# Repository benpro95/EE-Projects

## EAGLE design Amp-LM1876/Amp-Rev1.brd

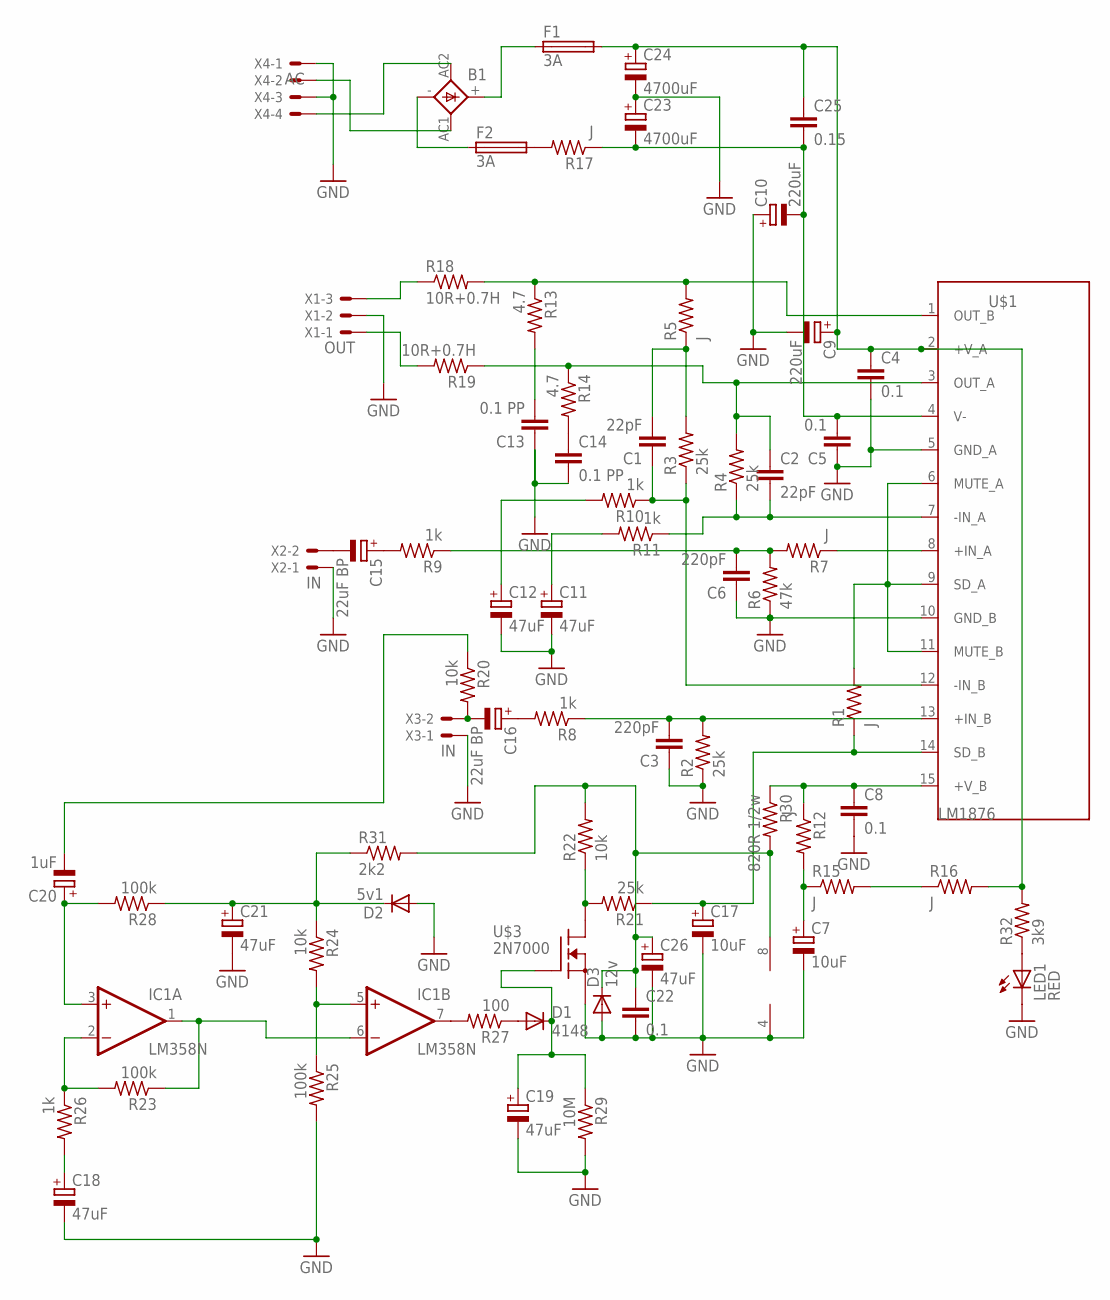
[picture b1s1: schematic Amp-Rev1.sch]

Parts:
B1: GBU4; GBU4S
C1, C2: 22pF; C075-032X103
C3, C6: 220pF; C1210
C4, C5, C8: 0.1; C050-025X075
C7: 10uF; E2,5-7
C9, C10: 220uF; E5-8,5
C11, C12, C18, C19, C21, C26: 47uF; E2,5-7
C13, C14: 0.1 PP; C050-055X075
C15, C16: 22uF BP; E2,5-7
C17: 10uF; E2,5-6
C20: 1uF; E2,5-6
C22: 0.1; C1206
C23, C24: 4700uF; E7,5-16
C25: 0.15; C075-032X103
D1: 4148; DO35-7
D2: 5v1; DO35-10
D3: 12v; DO35-10
F1, F2: 3A; 19560
IC1: LM358N; DIL08
LED1: RED; LED3MM
R1, R12, R15, R16: J; 0207/12
R2: 25k; R1210
R3, R4: 25k; 0207/10
R5, R17: J; 0207/10
R6: 47k; M1206
R7: J; 0204/7
R8, R11, R26: 1k; 0207/10
R9: 1k; 0207/12
R10: 1k; 0204/7
R13, R14: 4.7; 0207/12
R18, R19: 10R+0.7H; 0207/12
R20, R22: 10k; 0204/7
R21: 25k; 0204/7
R23, R25, R28: 100k; 0204/5
R24: 10k; 0207/10
R27: 100; 0204/7
R29: 10M; 0207/10
R30: 820R 1/2w; 0207/10
R31: 2k2; 0309/10
R32: 3k9; 0207/10
U$1: LM1876; MULTIWATT-15
U$3: 2N7000; TO92-
X1: OUT; 22-23-2031
X2, X3: IN; 22-23-2021
X4: AC; 5566-4

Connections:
GND: C3.1, C4.2, C5.1, C6.1, C7.-, C8.2, C9.-, C10.+, C11.-, C12.-, C13.1, C14.2, C17.-, C18.-, C19.-, C21.-, C22.2, C23.+, C24.-, C26.-, D2.A, D3.A, IC1.4 (V-), LED1.K (C), R2.1, R6.1, R25.2, R29.2, U$1.5 (GND_A), U$1.10 (GND_B), U$3.3 (S), X1.2, X2.1, X3.1, X4.1, X4.3
unnamed: R7.1, U$1.8 (+IN_A)
unnamed: R1.2, U$1.6 (MUTE_A), U$1.9 (SD_A), U$1.11 (MUTE_B)
unnamed: C1.2, R3.2, R5.1
unnamed: C6.2, R6.2, R7.2, R9.1
unnamed: C2.2, R4.1, R11.1, U$1.7 (-IN_A)
unnamed: C5.2, C10.-, C23.-, C25.2, R17.1, U$1.4 (V-)
unnamed: C2.1, R4.2, R14.1, R19.1, U$1.3 (OUT_A)
unnamed: C4.1, C9.+, C24.+, C25.1, F1.2, R16.2, R32.2, U$1.2 (+V_A)
unnamed: R5.2, R13.1, R18.2, U$1.1 (OUT_B)
unnamed: C1.1, R3.1, R10.1, U$1.12 (-IN_B)
unnamed: R15.2, R16.1
unnamed: C22.1, C26.+, D3.C, IC1.8 (V+), R22.2, R30.2, R31.2
unnamed: C7.+, R12.2, R15.1
unnamed: C17.+, R1.1, R21.1, U$1.14 (SD_B)
unnamed: C12.+, R10.2
unnamed: C11.+, R11.2
unnamed: C3.2, R2.2, R8.1, U$1.13 (+IN_B)
unnamed: C13.2, R13.2
unnamed: C14.1, R14.2
unnamed: R18.1, X1.3
unnamed: R19.2, X1.1
unnamed: C15.+, R9.2
unnamed: C15.-, X2.2
unnamed: C20.-, R20.1
unnamed: C16.+, R8.2
unnamed: C16.-, R20.2, X3.2
unnamed: LED1.A, R32.1
unnamed: C19.+, D1.C, R29.1, U$3.2 (G)
unnamed: IC1.2 (-IN), R23.2, R26.1
unnamed: IC1.1 (OUT), IC1.6 (-IN), R23.1
unnamed: C20.+, IC1.3 (+IN), R28.2
unnamed: IC1.5 (+IN), R24.2, R25.1
unnamed: C18.+, R26.2
unnamed: C8.1, R12.1, R30.1, U$1.15 (+V_B)
unnamed: IC1.7 (OUT), R27.2
unnamed: C21.+, D2.C, R24.1, R28.1, R31.1
unnamed: R21.2, R22.1, U$3.1 (D)
unnamed: D1.A, R27.1
unnamed: B1.+, F1.1
unnamed: F2.2, R17.2
unnamed: B1.-, F2.1
unnamed: B1.AC1 (AC2), X4.2
unnamed: B1.AC2 (AC1), X4.4

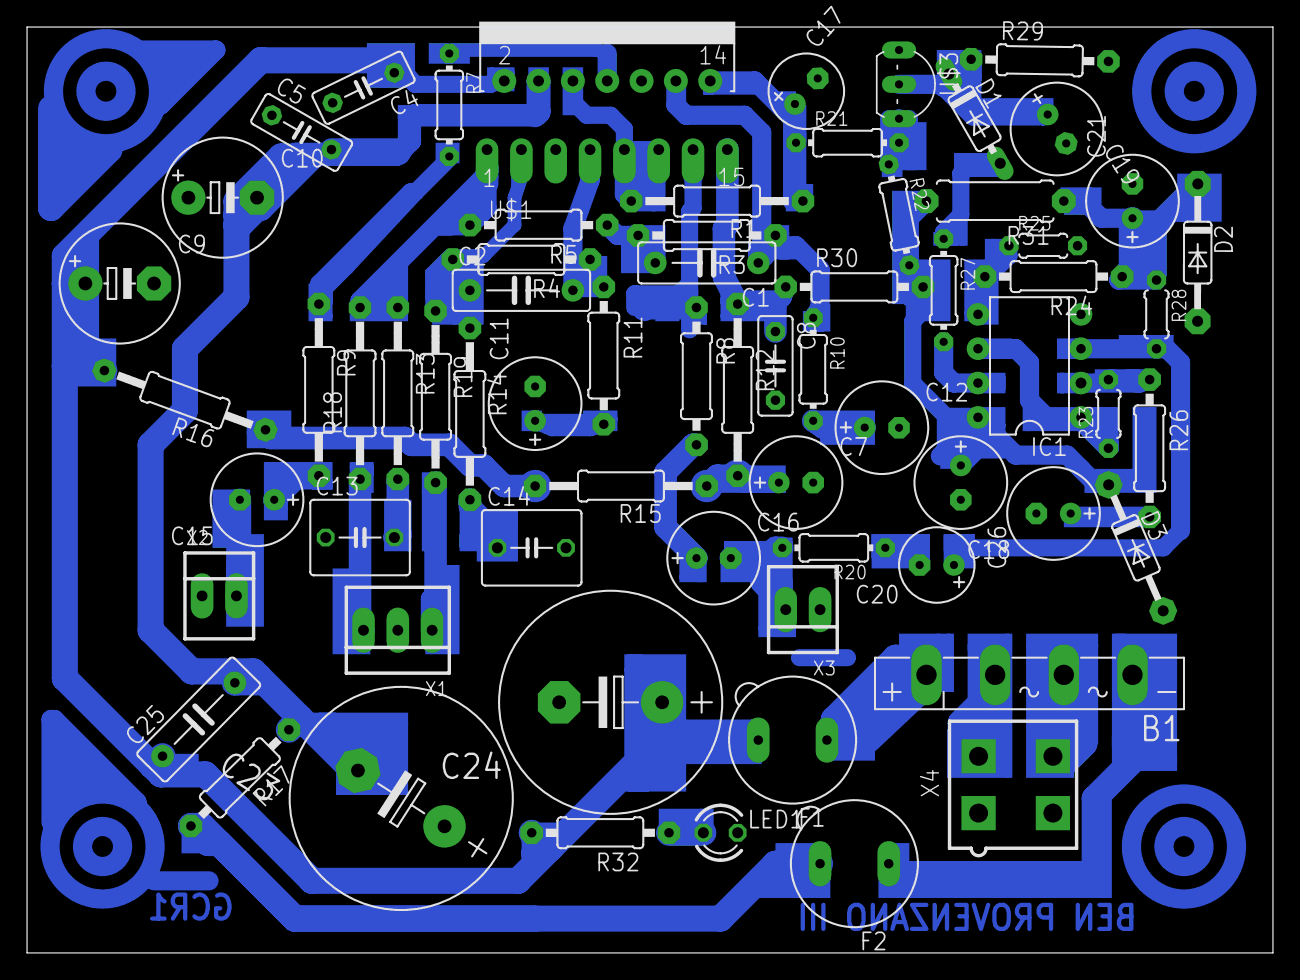
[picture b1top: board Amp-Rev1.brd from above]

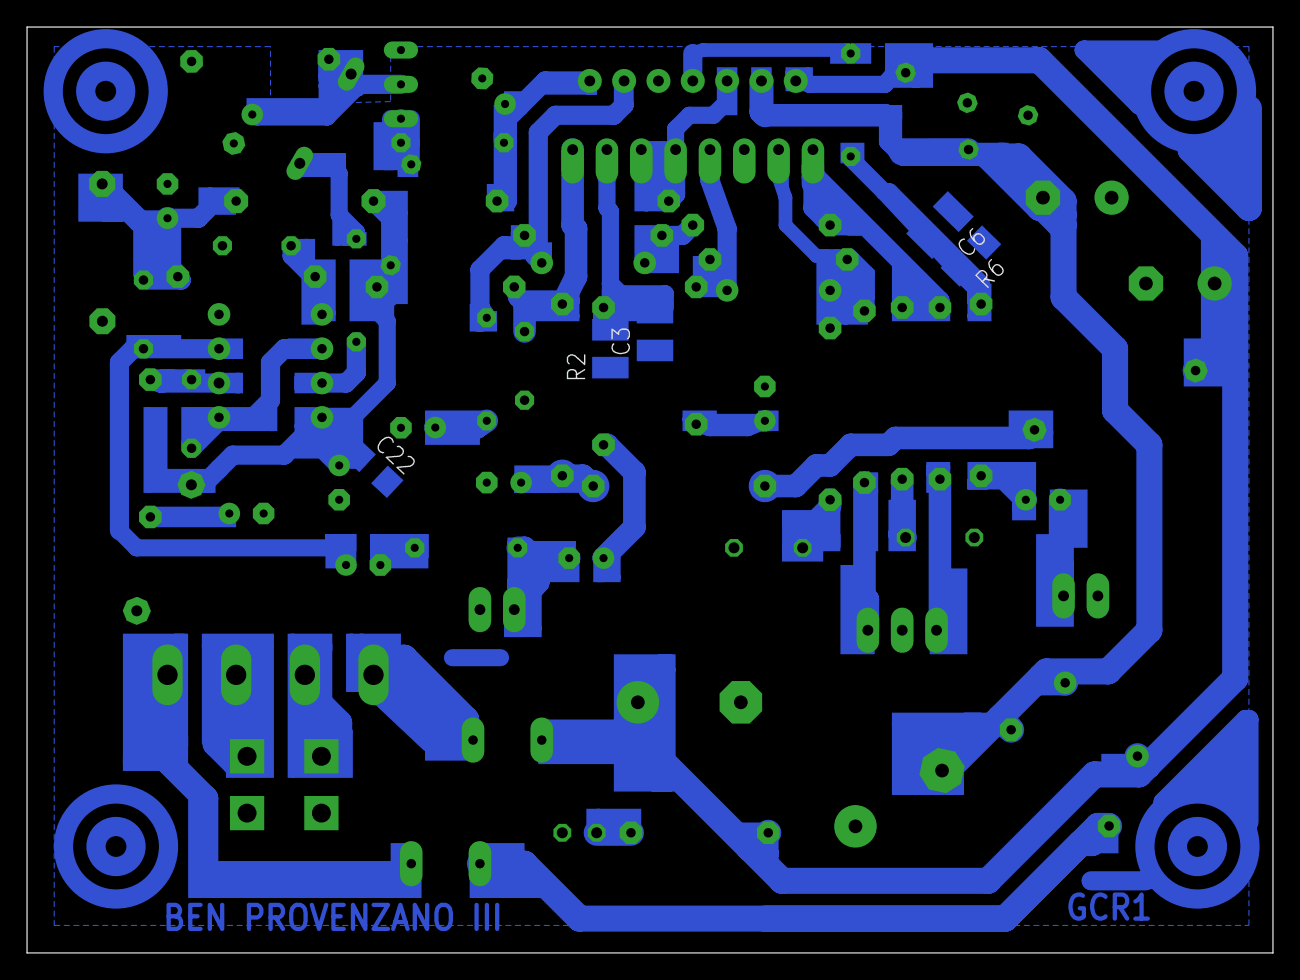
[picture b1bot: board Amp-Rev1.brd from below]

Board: 2 copper layers, 92.2 x 68.5 mm, 72 parts (5 on the bottom side), 44 nets.

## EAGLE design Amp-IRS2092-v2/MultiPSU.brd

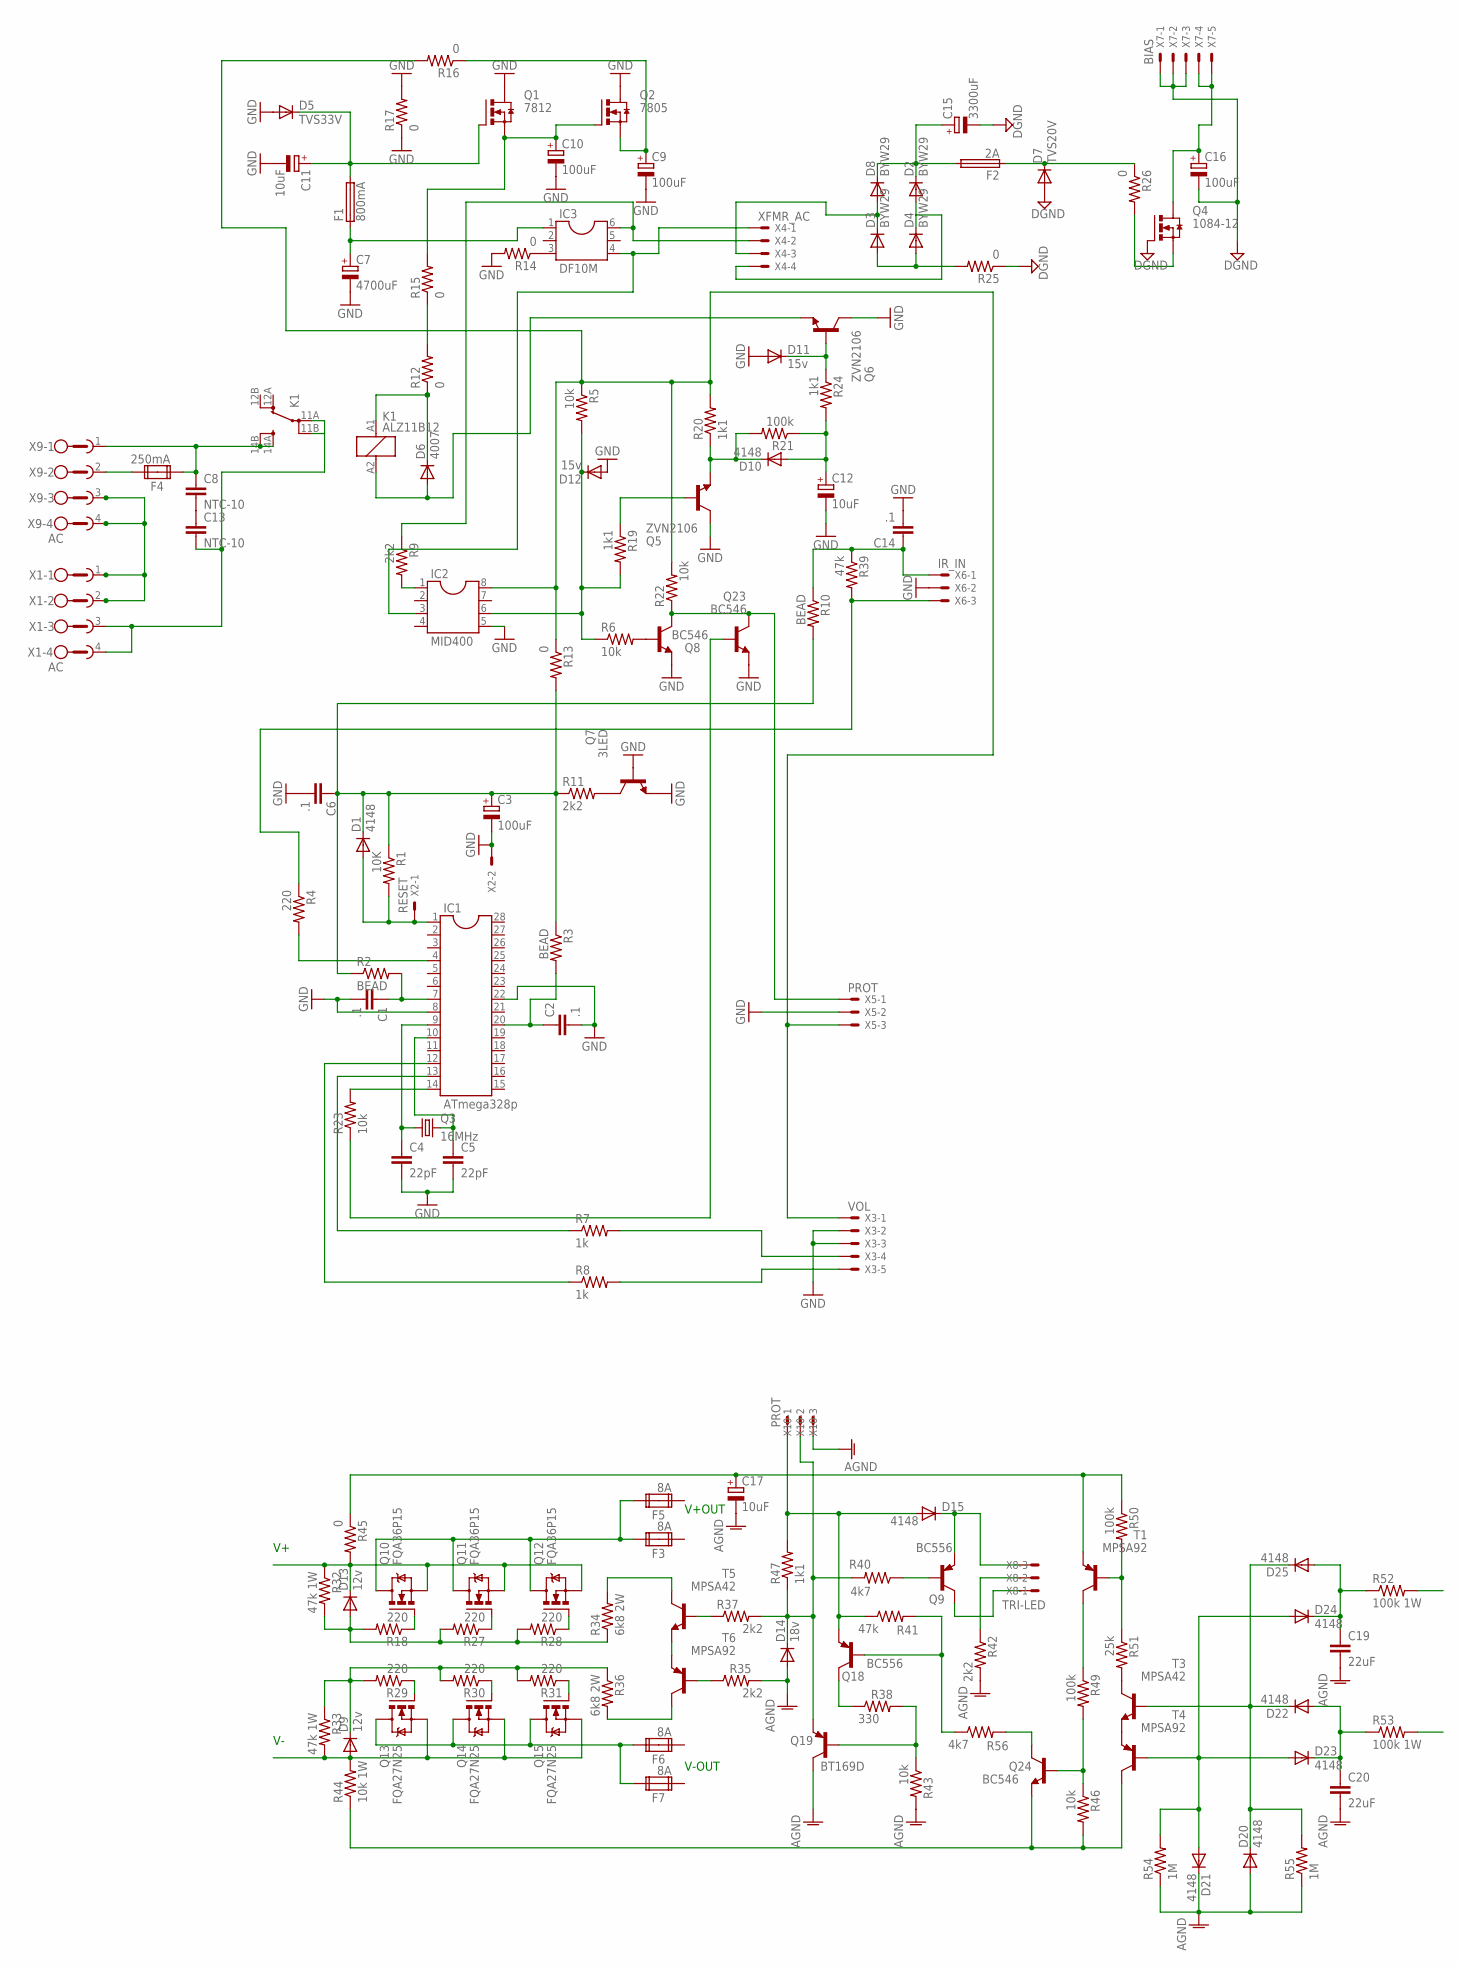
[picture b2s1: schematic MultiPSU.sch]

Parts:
C1, C2, C6, C14: .1; C1210K
C3, C9, C10, C16: 100uF; E3,5-10
C4, C5: 22pF; C1210K
C7: 4700uF; E7,5-16
C8, C13: NTC-10; C102-054X133
C11, C12, C17: 10uF; E3,5-10
C15: 3300uF; E7,5-16
C19, C20: 22uF; C050-075X075
D1, D20, D21, D22, D23, D24, D25: 4148; DO35-7
D2, D3, D4, D8: BYW29; DO220S
D5: TVS33V; SOD57-10
D6: 4007; DO41-10
D7: TVS20V; SOD57-10
D9, D13: 12v; DO41-10
D10: 4148; DO35-10
D11, D12: 15v; DO35-7
D14: 18v; DO41-10
D15: 4148; DO41-10
F1: 800mA; 19560
F2: 2A; 19560
F3, F5, F6, F7: 8A; FUSE1
F4: 250mA; FUSE1
IC1: ATmega328p; DIL28-3
IC2: MID400; DIL08
IC3: DF10M; DIL06
K1: ALZ11B12; RT-C/O16A5
Q1: 7812; TO220BH
Q2: 7805; TO220BH
Q3: 16MHz; HC49/S
Q4: 1084-12; TO220BH
Q5, Q6: ZVN2106; TO92-EBC
Q7: 3LED; TO92-EBC
Q8, Q23, Q24: BC546; TO92-EBC
Q9, Q18: BC556; TO92-EBC
Q10, Q11, Q12: FQA36P15; TO-247AD-H
Q13, Q14, Q15: FQA27N25; TO-247AD-H
Q19: BT169D; TO92-EBC
R1: 10K; 0309/10
R2, R10: BEAD; 0309/10
R3: BEAD; 0309/12
R4, R18, R27, R28, R29, R30, R31: 220; 0309/12
R5, R22, R43: 10k; 0309/10
R6: 10k; 0309/12
R7, R8: 1k; R1210
R9: 2k2; 0309/12
R11, R35, R37, R42: 2k2; 0309/10
R12, R14: 0; 0309/10
R13, R15, R16, R17, R25, R26, R45: 0; 0309/12
R19: 1k1; 0309/12
R20, R24, R47: 1k1; 0309/10
R21, R50: 100k; 0309/10
R23: 10k; R1210
R32, R33: 47k 1W; 0411/15
R34, R36: 6k8 2W; 0411/15
R38: 330; 0309/10
R39, R41: 47k; 0309/10
R40, R56: 4k7; 0309/10
R44: 10k 1W; 0411/15
R46: 10k; 0411/15
R49: 100k; 0411/15
R51: 25k; 0309/10
R52, R53: 100k 1W; 0309/10
R54, R55: 1M; R1210
T1, T4, T6: MPSA92; TO92-EBC
T3, T5: MPSA42; TO92-EBC
X1, X9: AC; GMSTBA4
X2: RESET; 22-23-2021
X3: VOL; 22-23-2051
X4: XFMR_AC; 5566-4
X5, X10: PROT; 22-23-2031
X6: IR_IN; 22-23-2031
X7: BIAS; 22-23-2051
X8: TRI-LED; 22-23-2031

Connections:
AGND: C17.-, C19.2, C20.2, D14.A, D20.A, D21.C, Q19.C, R35.2, R42.2, R43.2, R54.1, R55.1, X10.3
DGND: C15.-, C16.-, D7.A, Q4.G, R25.1, X7.1, X7.2, X7.3
GND: C1.2, C2.2, C3.-, C4.2, C5.2, C6.2, C7.-, C9.-, C10.-, C11.-, C12.-, C14.2, D5.A, D11.A, D12.A, IC1.8, IC1.22, IC2.5, Q1.D, Q2.D, Q5.C, Q6.C, Q7.B, Q7.E, Q8.E, Q23.E, R14.2, R17.1, R17.2, X2.2, X3.2, X3.3, X5.2, X6.2
unnamed: Q8.B, R6.2
unnamed: D1.A, IC1.1, R1.2, X2.1
unnamed: IC1.4, R4.2
unnamed: C2.1, IC1.20, R3.2
unnamed: R4.1, R39.2, X6.3
unnamed: IC1.13, R7.1
unnamed: IC1.12, R8.1
unnamed: C11.+, D5.C, F1.2, Q1.G
unnamed: C8.2, C13.1
unnamed: D6.C, K1.A1 (1), R12.1
unnamed: IC3.6, R9.1, X4.2
unnamed: C4.1, IC1.9, Q3.1
unnamed: C5.1, IC1.10, Q3.2
unnamed: X1.1, X1.2, X9.3, X9.4
unnamed: D12.C, IC2.6, R5.2, R6.1, R19.2
unnamed: IC2.1, R9.2
unnamed: Q8.C, Q23.C, R22.1, X5.1
unnamed: IC3.3, R14.1
unnamed: C14.1, R10.1, R39.1, X6.1
unnamed: F4.2A, X9.2
unnamed: Q7.C, R11.2
unnamed: C8.1, F4.1A, K1.14A (SA), K1.14B (SB), X9.1
unnamed: C13.2, K1.11A (PA), K1.11B (PB), X1.3, X1.4
unnamed: C9.+, Q2.S, R16.1
unnamed: C10.+, Q1.S, Q2.G, R15.2
unnamed: R12.2, R15.1
unnamed: C7.+, F1.1, IC3.1
unnamed: C3.+, C6.1, D1.C, R1.1, R2.1, R3.1, R10.2, R11.1, R13.2
unnamed: D3.C, D8.A, X4.3
unnamed: D2.A, D4.C, X4.4
unnamed: C1.1, IC1.7, R2.2
unnamed: IC2.8, R5.1, R13.1, R16.2, R20.2, R22.2, X3.1, X5.3
unnamed: IC2.3, IC3.4, X4.1
unnamed: Q5.B, R19.1
unnamed: D10.C, Q5.E, R20.1, R21.2
unnamed: C12.+, D10.A, R21.1, R24.2
unnamed: IC1.14, R23.2
unnamed: D6.A, K1.A2 (2), Q6.E
unnamed: D11.C, Q6.B, R24.1
unnamed: Q23.B, R23.1
unnamed: R8.2, X3.5
unnamed: R7.2, X3.4
unnamed: D3.A, D4.A, R25.2
unnamed: C15.+, D2.C, D8.C, F2.2
unnamed: D7.C, F2.1, R26.1
unnamed: Q4.S, R26.2
unnamed: D13.C, Q10.S, Q11.S, Q12.S, R32.1, R45.2
unnamed: F3.2A, F5.2A, Q10.D, Q11.D, Q12.D
unnamed: D9.A, Q13.S, Q14.S, Q15.S, R33.2, R44.2
unnamed: C16.+, Q4.D, X7.4, X7.5
unnamed: F6.2A, F7.2A, Q13.D, Q14.D, Q15.D
unnamed: Q10.G, R18.1
unnamed: Q11.G, R27.1
unnamed: Q12.G, R28.1
unnamed: Q13.G, R29.1
unnamed: Q14.G, R30.1
unnamed: Q15.G, R31.1
unnamed: D9.C, R29.2, R30.2, R31.2, R33.1, R36.1
unnamed: D13.A, R18.2, R27.2, R28.2, R32.2, R34.1
unnamed: R34.2, T5.C
unnamed: R36.2, T6.C
unnamed: T5.E, T6.E
unnamed: R35.1, T6.B
unnamed: R37.1, T5.B
unnamed: Q18.C, R38.1
unnamed: D14.C, Q19.E, R37.2, R40.2, R47.1, X10.2
unnamed: Q9.B, R40.1
unnamed: R42.1, X8.2
unnamed: Q19.B, R38.2, R43.1
unnamed: Q9.C, X8.1
unnamed: D15.C, Q9.E, X8.3
unnamed: Q24.E, R44.1, R46.2, T4.C
unnamed: R49.1, T1.C
unnamed: Q24.B, R46.1, R49.2
unnamed: C17.+, R45.1, R50.1, T1.E
unnamed: Q18.B, R41.2, R56.1
unnamed: R50.2, R51.1, T1.B
unnamed: R51.2, T3.C
unnamed: T3.E, T4.E
unnamed: D21.A, D23.A, D24.A, R54.2, T4.B
unnamed: D20.C, D22.C, D25.C, R55.2, T3.B
unnamed: C20.1, D22.A, D23.C, R53.1
unnamed: C19.1, D24.C, D25.A, R52.1
unnamed: Q24.C, R56.2
unnamed: D15.A, Q18.E, R41.1, R47.2, X10.1

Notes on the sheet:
V+OUT
V-OUT

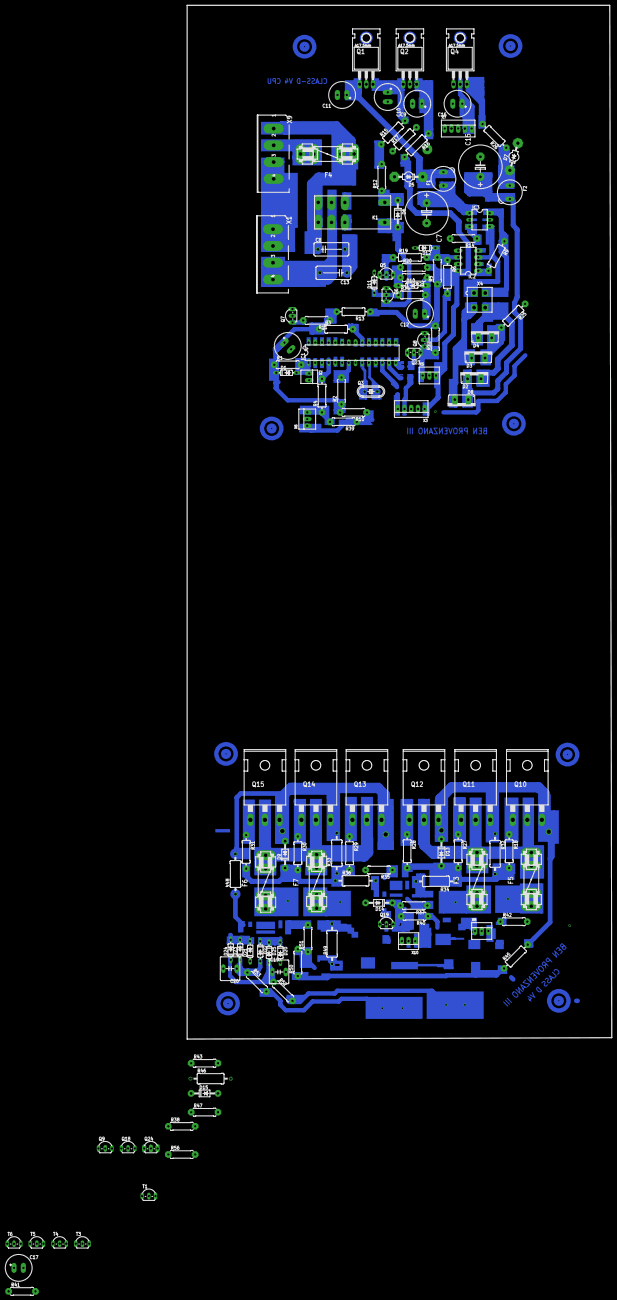
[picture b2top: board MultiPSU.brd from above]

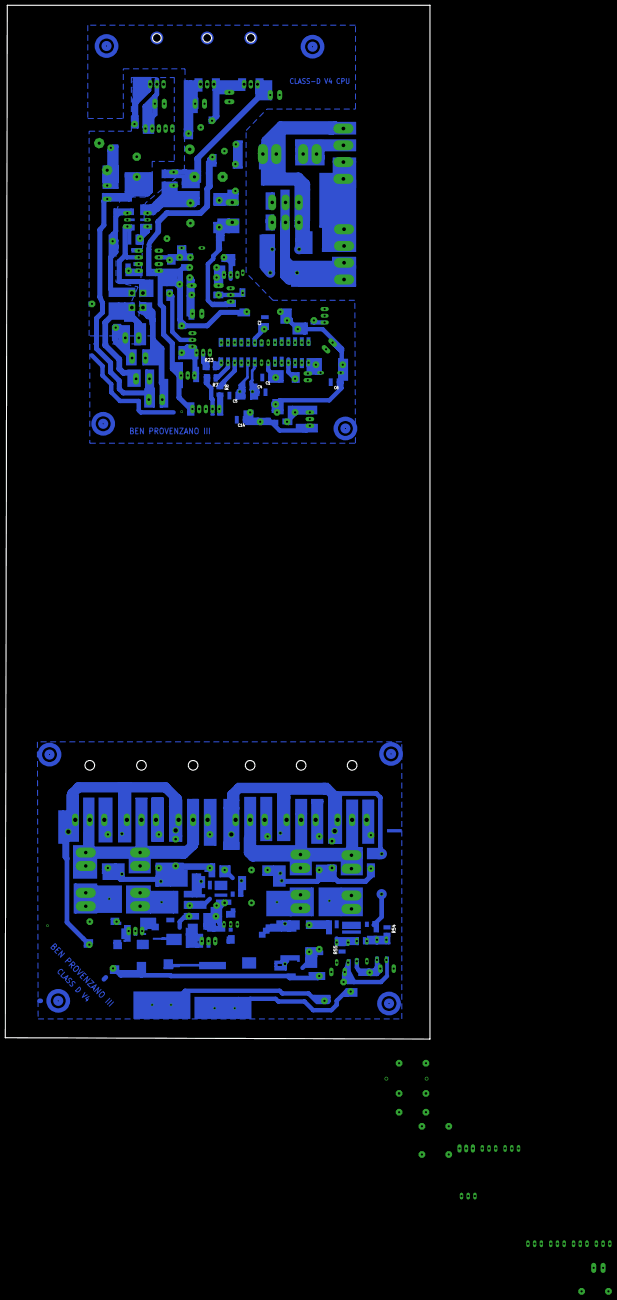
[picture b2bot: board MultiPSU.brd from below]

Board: 2 copper layers, 160.8 x 391.3 mm, 140 parts (11 on the bottom side), 88 nets.

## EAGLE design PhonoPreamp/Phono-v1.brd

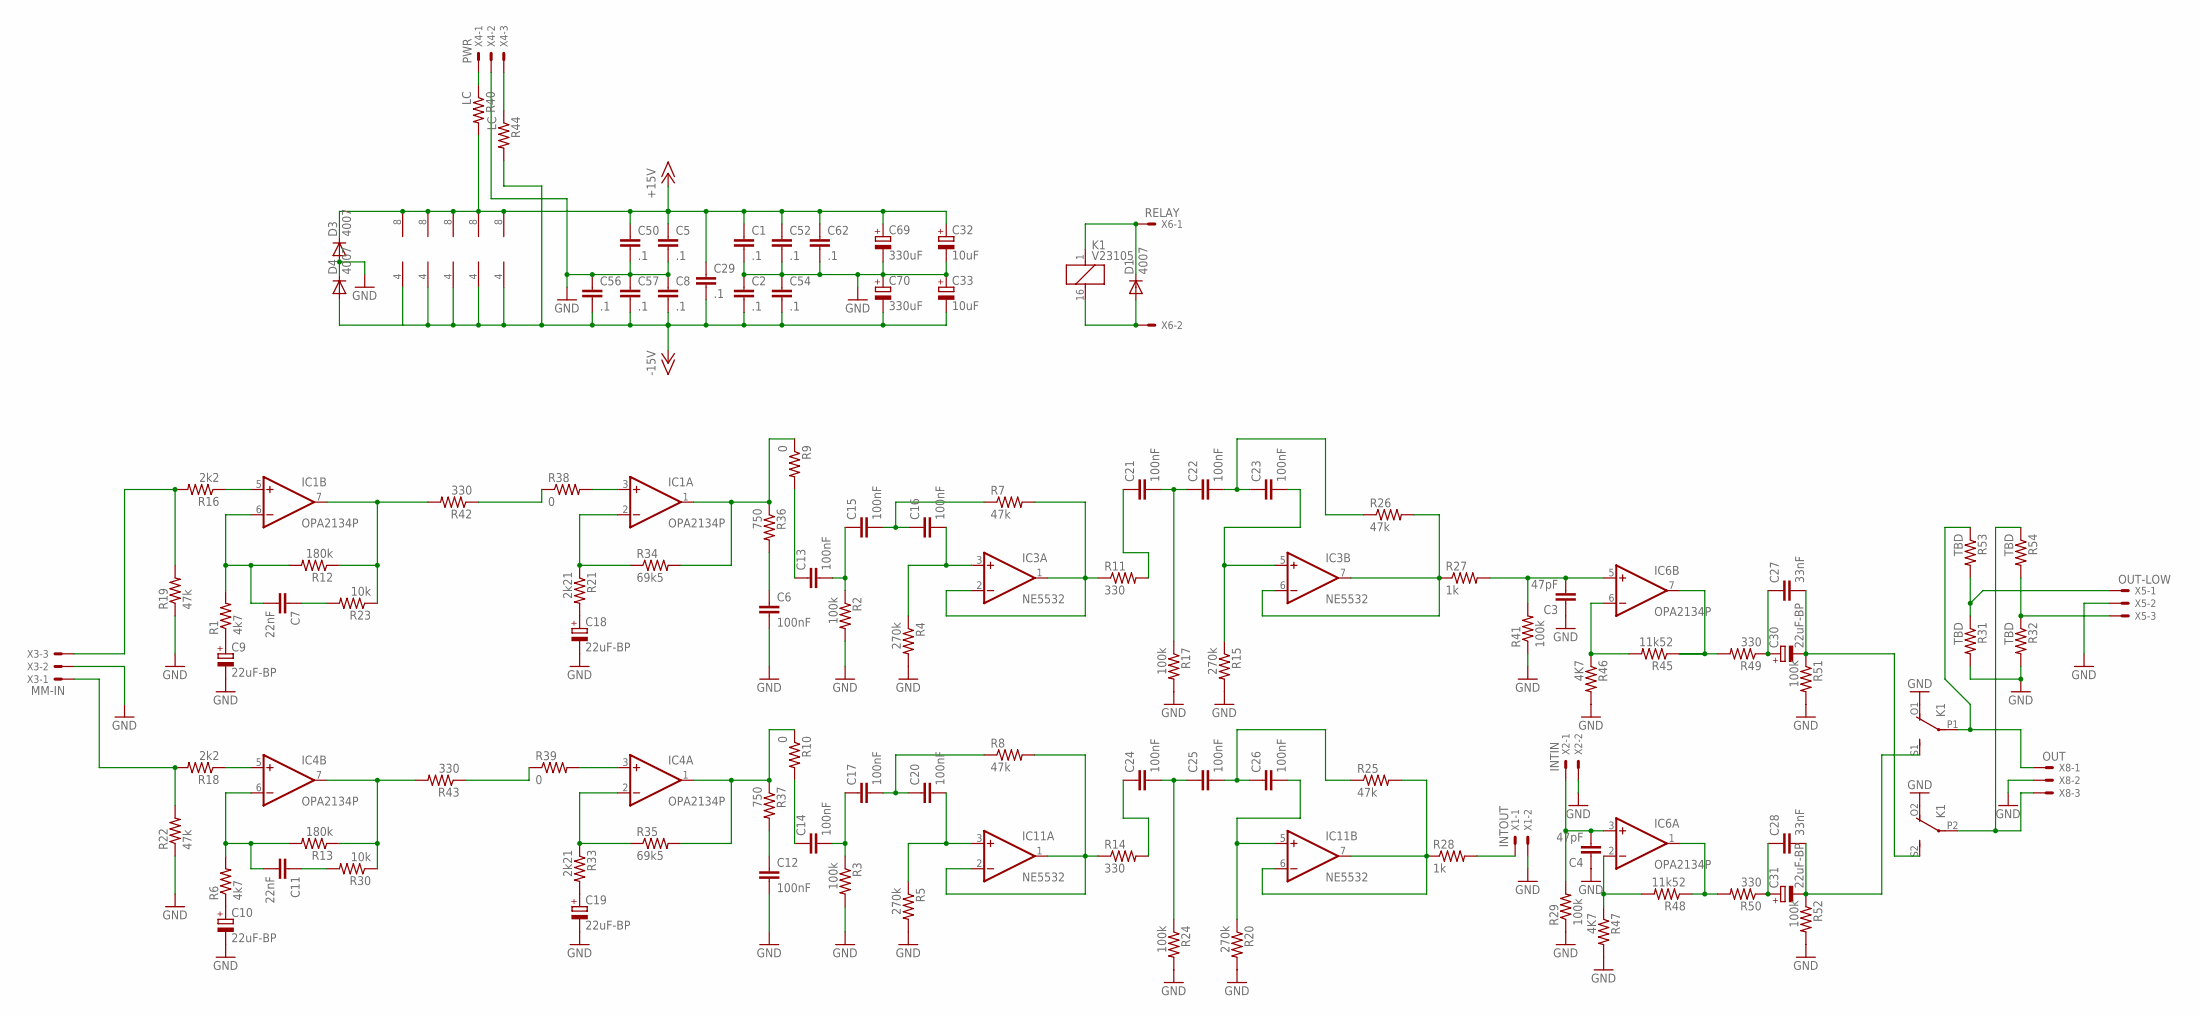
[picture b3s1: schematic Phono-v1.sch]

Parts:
C1, C2, C5, C8, C29, C50, C52, C54, C56, C57, C62: .1; C4532
C3, C4: 47pF; C1210
C6, C12, C13, C14, C15, C16, C17, C20, C21, C22, C23, C24, C25, C26: 100nF; C050-075X075
C7, C11: 22nF; C050-075X075
C9, C10, C18, C19, C30, C31: 22uF-BP; E5-10,5
C27, C28: 33nF; C050-075X075
C32, C33: 10uF; E2-5
C69, C70: 330uF; E5-10,5
D1: 4007; DO35-7
D3, D4: 4007; DO35-10
IC1, IC4, IC6: OPA2134P; DIL08
IC3, IC11: NE5532; DIL08
K1: V23105; 351
R1, R6: 4k7; 0309/10
R2, R3, R17, R24, R29, R41, R51, R52: 100k; 0309/10
R4, R5, R15, R20: 270k; 0309/10
R7, R8, R19, R22, R25, R26: 47k; 0309/10
R9: 0; 0309/10
R10: 0; 0309/12
R11, R14, R42, R43, R49, R50: 330; 0309/10
R12, R13: 180k; 0309/10
R16, R18: 2k2; 0309/10
R21, R33: 2k21; 0309/10
R23, R30: 10k; 0309/10
R27: 1k; 0309/10
R28: 1k; 0309/12
R31, R32, R53, R54: TBD; 0309/10
R34, R35: 69k5; 0309/10
R36, R37: 750; 0309/10
R38: 0; 0207/7
R39: 0; 0204/7
R40, R44: LC; 0309/12
R45, R48: 11k52; 0309/10
R46, R47: 4K7; 0309/10
X1: INTOUT; 22-23-2021
X2: INTIN; 22-23-2021
X3: MM-IN; 22-23-2031
X4: PWR; 22-23-2031
X5: OUT-LOW; 22-23-2031
X6: RELAY; 22-23-2021
X8: OUT; 22-23-2031

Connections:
+15V: C1.1, C5.1, C29.1, C32.+, C50.1, C52.1, C62.1, C69.+, D3.C, IC1.8 (V+), IC3.8 (V+), IC4.8 (V+), IC6.8 (V+), IC11.8 (V+), R40.2
-15V: C2.2, C8.2, C29.2, C33.-, C54.2, C56.2, C57.2, C70.-, D4.A, IC1.4 (V-), IC3.4 (V-), IC4.4 (V-), IC6.4 (V-), IC11.4 (V-), R44.2
GND: C1.2, C2.1, C3.1, C4.1, C5.2, C6.2, C8.1, C9.-, C10.-, C12.2, C18.-, C19.-, C32.-, C33.+, C50.2, C52.2, C54.1, C56.1, C57.1, C62.2, C69.-, C70.+, D3.A, D4.C, K1.O1 (O), K1.O2 (O), R2.2, R3.2, R4.2, R5.2, R15.2, R17.2, R19.1, R20.2, R22.1, R24.2, R29.1, R31.2, R32.2, R41.1, R46.2, R47.2, R51.2, R52.2, X1.2, X2.2, X3.2, X4.2, X5.2, X8.2
unnamed: C13.2, C15.1, R2.1
unnamed: C14.2, C17.1, R3.1
unnamed: R31.1, R53.2, X5.1
unnamed: C13.1, R9.2
unnamed: C14.1, R10.2
unnamed: IC3.6 (-IN), IC3.7 (OUT), R26.2, R27.1
unnamed: IC11.1 (OUT), IC11.2 (-IN), R8.2, R14.1
unnamed: IC11.6 (-IN), IC11.7 (OUT), R25.2, R28.1
unnamed: C26.2, IC11.5 (+IN), R20.1
unnamed: R39.1, R43.1
unnamed: R38.1, R42.1
unnamed: C23.2, IC3.5 (+IN), R15.1
unnamed: C16.2, IC3.3 (+IN), R4.1
unnamed: IC1.5 (+IN), R16.1
unnamed: C17.2, C20.1, R8.1
unnamed: C21.1, R11.2
unnamed: C15.2, C16.1, R7.1
unnamed: IC4.5 (+IN), R18.1
unnamed: IC1.7 (OUT), R12.1, R23.1, R42.2
unnamed: IC4.7 (OUT), R13.1, R30.1, R43.2
unnamed: C11.2, IC4.6 (-IN), R6.2, R13.2
unnamed: C7.2, IC1.6 (-IN), R1.2, R12.2
unnamed: R18.2, R22.2, X3.1
unnamed: C20.2, IC11.3 (+IN), R5.1
unnamed: C24.1, R14.2
unnamed: C21.2, C22.1, R17.1
unnamed: C22.2, C23.1, R26.1
unnamed: C24.2, C25.1, R24.1
unnamed: R16.2, R19.2, X3.3
unnamed: IC1.2 (-IN), R21.1, R34.1
unnamed: IC4.2 (-IN), R33.1, R35.1
unnamed: K1.P2, R54.1, X8.3
unnamed: K1.P1, R53.1, X8.1
unnamed: C7.1, R23.2
unnamed: C9.+, R1.1
unnamed: IC1.3 (+IN), R38.2
unnamed: IC1.1 (OUT), R9.1, R34.2, R36.1
unnamed: D1.A, K1.16 (2), X6.2
unnamed: D1.C, K1.1, X6.1
unnamed: IC4.1 (OUT), R10.1, R35.2, R37.1
unnamed: C6.1, R36.2
unnamed: C12.1, R37.2
unnamed: C18.+, R21.2
unnamed: C19.+, R33.2
unnamed: IC4.3 (+IN), R39.2
unnamed: C10.+, R6.1
unnamed: C25.2, C26.1, R25.1
unnamed: IC3.1 (OUT), IC3.2 (-IN), R7.2, R11.1
unnamed: C11.1, R30.2
unnamed: C3.2, IC6.5 (+IN), R27.2, R41.2
unnamed: R28.2, X1.1
unnamed: C4.2, IC6.3 (+IN), R29.2, X2.1
unnamed: R40.1, X4.1
unnamed: R44.1, X4.3
unnamed: IC6.6 (-IN), R45.2, R46.1
unnamed: C28.2, C31.-, K1.S1 (S), R52.1
unnamed: C27.1, C30.+, R49.1
unnamed: IC6.2 (-IN), R47.1, R48.2
unnamed: C28.1, C31.+, R50.1
unnamed: C27.2, C30.-, K1.S2 (S), R51.1
unnamed: IC6.7 (OUT), R45.1, R49.2
unnamed: IC6.1 (OUT), R48.1, R50.2
unnamed: R32.1, R54.2, X5.3

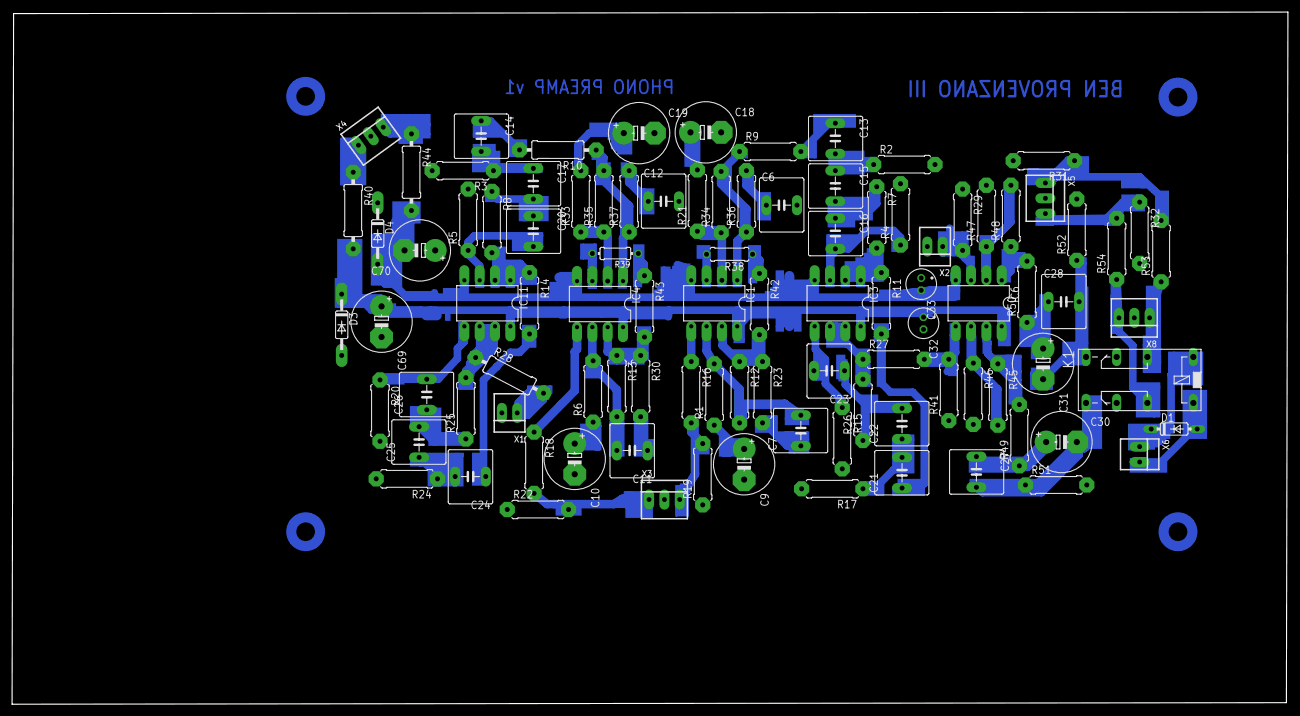
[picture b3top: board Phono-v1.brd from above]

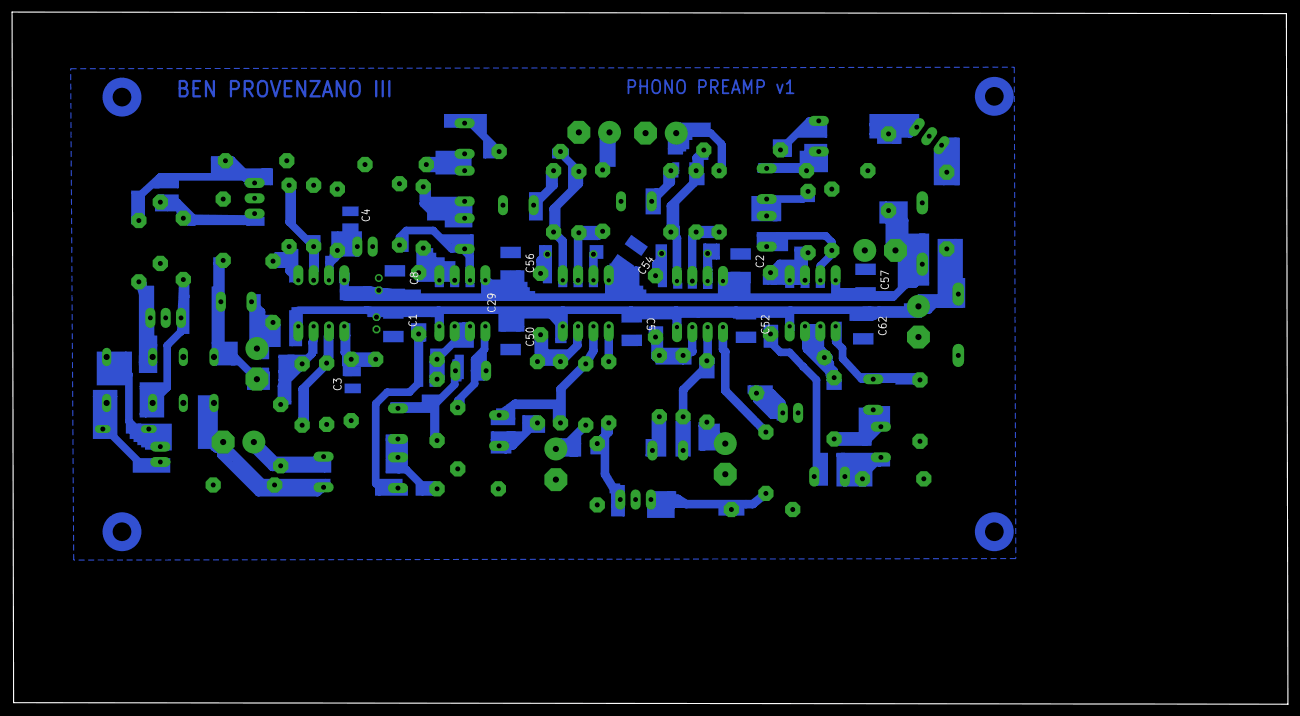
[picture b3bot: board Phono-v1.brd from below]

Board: 2 copper layers, 211.4 x 114.7 mm, 111 parts (13 on the bottom side), 66 nets.

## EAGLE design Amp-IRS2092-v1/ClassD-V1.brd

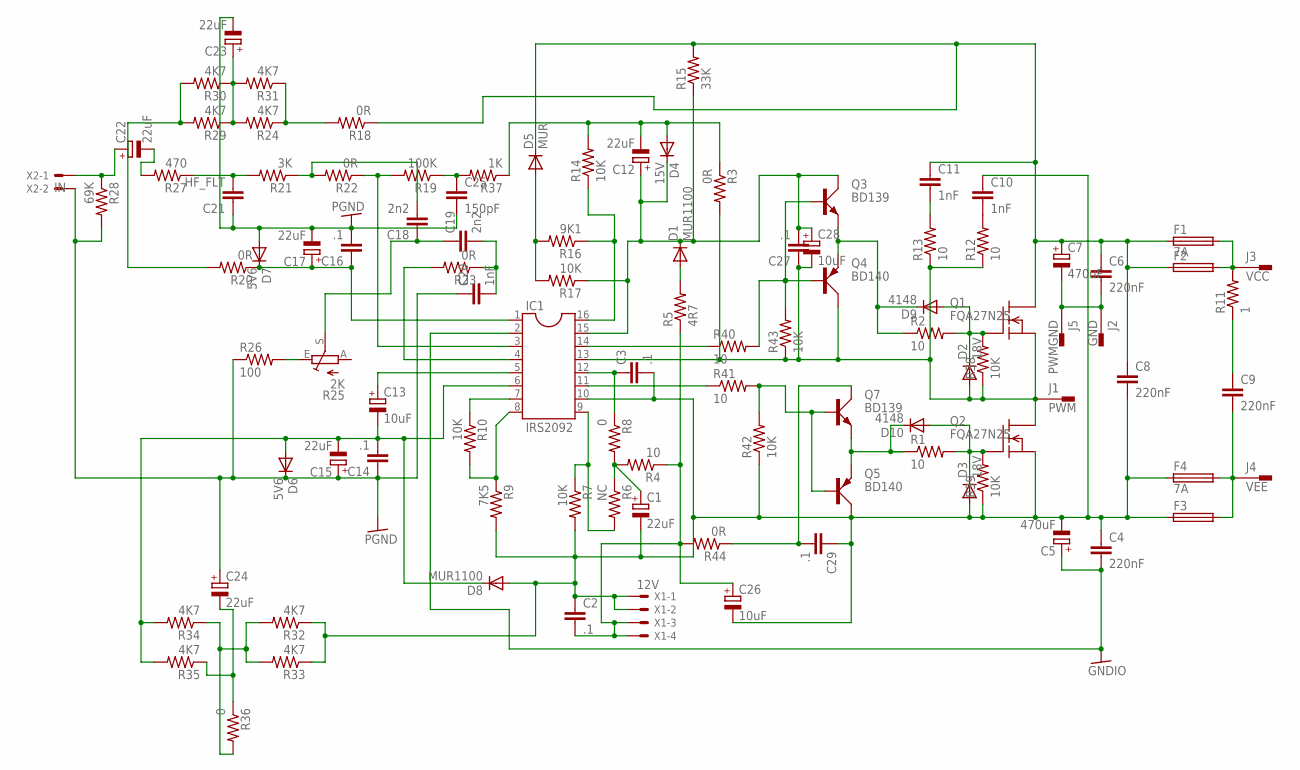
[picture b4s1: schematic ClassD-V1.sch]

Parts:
C1, C12, C15, C17, C22, C23, C24: 22uF; E5-10,5
C2, C3, C14, C16, C27, C29: .1; C1210K
C4, C6, C8, C9: 220nF; C22.5B11
C5, C7: 470uF; E7,5-16
C10, C11, C20: 1nF; C5B3.5
C13, C26, C28: 10uF; E3,5-8
C18, C19: 2n2; C5B3.5
C21: HF_FLT; C5B3.5
C25: 150pF; C5B3.5
D1, D8: MUR1100; DO41-10
D2, D3: 18V; DO35-10
D4: 15V; DO35-7
D5: MUR; DO35-10
D6: 5V6; DO35-10
D7: 5V6; DO35-7
D9, D10: 4148; DO35-10
F1, F4: 7A; KS9V
F2, F3: KS9V
IC1: IRS2092; DIL16
J1: PWM; F061.040
J2: GND; F061.040
J3: VCC; F061.040
J4: VEE; F061.040
J5: PWMGND; F061.040
Q1, Q2: FQA27N25; TOP3
Q3, Q7: BD139; TO126AV
Q4, Q5: BD140; TO126AV
R1, R2, R4, R40: 10; 0207/10
R3: 0R; 0207/12
R5: 4R7; 0207/10
R6: NC; 0207/10
R7, R10, R14, R17, R38, R39, R42, R43: 10K; 0207/10
R8, R36: 0; 0207/10
R9: 7K5; 0207/10
R11: 1; 0207/10
R12, R13: 10; 0309/12
R15: 33K; 0207/10
R16: 9K1; 0207/10
R18, R20, R22, R23: 0R; 0207/10
R19: 100K; 0207/10
R21: 3K; 0207/10
R24, R29, R30, R31, R32, R33, R34, R35: 4K7; 0617/22
R25: 2K; CT6
R26: 100; 0207/10
R27: 470; 0207/10
R28: 69K; 0207/10
R37: 1K; 0207/10
R41: 10; 0207/12
R44: 0R; 0204/7
X1: 12V; 22-23-2041
X2: IN; 22-23-2021

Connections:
COM: C1.-, C2.1, C3.2, C4.1, C5.-, C8.2, C10.1, C26.-, C29.1, D3.A, D8.A, F3.1, F4.1, IC1.10, Q2.3 (S), Q5.C, R7.2, R9.2, R32.1, R33.1, R39.1, R42.1, X1.1, X1.2
unnamed: D2.C, D9.A, Q1.1 (G), R2.2, R38.2
unnamed: D3.C, D10.A, Q2.1 (G), R1.2, R39.2
unnamed: IC1.8, R9.1, R10.2
unnamed: C6.1, C7.+, C8.1, C11.1, D5.C, F1.1, F2.1, Q1.2 (D), R15.2, R18.1
unnamed: IC1.14, R40.1
unnamed: IC1.11, R41.1
unnamed: D1.A, R5.2
unnamed: C9.2, F3.2, F4.2, J4.A1, J4.A2
unnamed: C3.1, IC1.12, R8.1
unnamed: C12.+, C27.2, C28.+, D1.C, D4.C, IC1.15, Q3.C, R15.1, R17.1
unnamed: IC1.9, R6.2, R7.1
unnamed: C1.+, R4.2, R6.1, R8.2
unnamed: C9.1, R11.1
unnamed: C11.2, R13.2
unnamed: D9.C, Q3.E, Q4.E, R2.1
unnamed: R25.E, R26.2
unnamed: C2.2, C26.+, R4.1, R5.1, R44.2, X1.3, X1.4
unnamed: IC1.7, R10.1
unnamed: F1.2, F2.2, J3.A1, J3.A2, R11.2
unnamed: C10.2, R12.2
unnamed: IC1.16, R14.1, R16.1
unnamed: D5.A, R16.2, R17.2
unnamed: C13.+, IC1.5
unnamed: C25.1, R19.1, R37.2
unnamed: IC1.3, R19.2, R22.1
unnamed: C18.1, C19.1, R25.S
unnamed: C19.2, C20.2, R23.1
unnamed: C18.2, R21.1, R22.2
unnamed: IC1.4, R23.2
unnamed: R18.2, R24.1, R31.1
unnamed: C21.2, R21.2, R27.1
unnamed: C22.-, R27.2
unnamed: C22.+, R28.1, X2.1
unnamed: C24.-, R35.1, R36.1
unnamed: C23.+, R24.2, R29.1, R30.1, R31.2
unnamed: R20.2, R29.2, R30.2
unnamed: R32.2, R33.2, R34.1, R36.2
unnamed: C13.-, C14.2, C15.-, D6.A, D8.C, IC1.6, R34.2, R35.2
unnamed: C12.-, D4.A, R3.1, R14.2, R37.1
unnamed: C27.1, C28.-, D2.A, IC1.13, J1.A1, J1.A2, Q1.3 (S), Q2.2 (D), Q4.C, R3.2, R12.1, R13.1, R38.1, R43.1
unnamed: Q5.B, Q7.B, R41.2, R42.2
unnamed: Q3.B, Q4.B, R40.2, R43.2
unnamed: C29.2, Q7.C, R44.1
unnamed: D10.C, Q5.E, Q7.E, R1.1
PGND: C4.2, C5.+, C6.2, C7.-, C14.1, C15.+, C16.2, C17.-, C20.1, C21.1, C23.-, C24.+, C25.2, D6.C, D7.A, IC1.2, J2.A1, J2.A2, J5.A1, J5.A2, R26.1, R28.2, X2.2
PGND1: C16.1, C17.+, D7.C, IC1.1, R20.1
